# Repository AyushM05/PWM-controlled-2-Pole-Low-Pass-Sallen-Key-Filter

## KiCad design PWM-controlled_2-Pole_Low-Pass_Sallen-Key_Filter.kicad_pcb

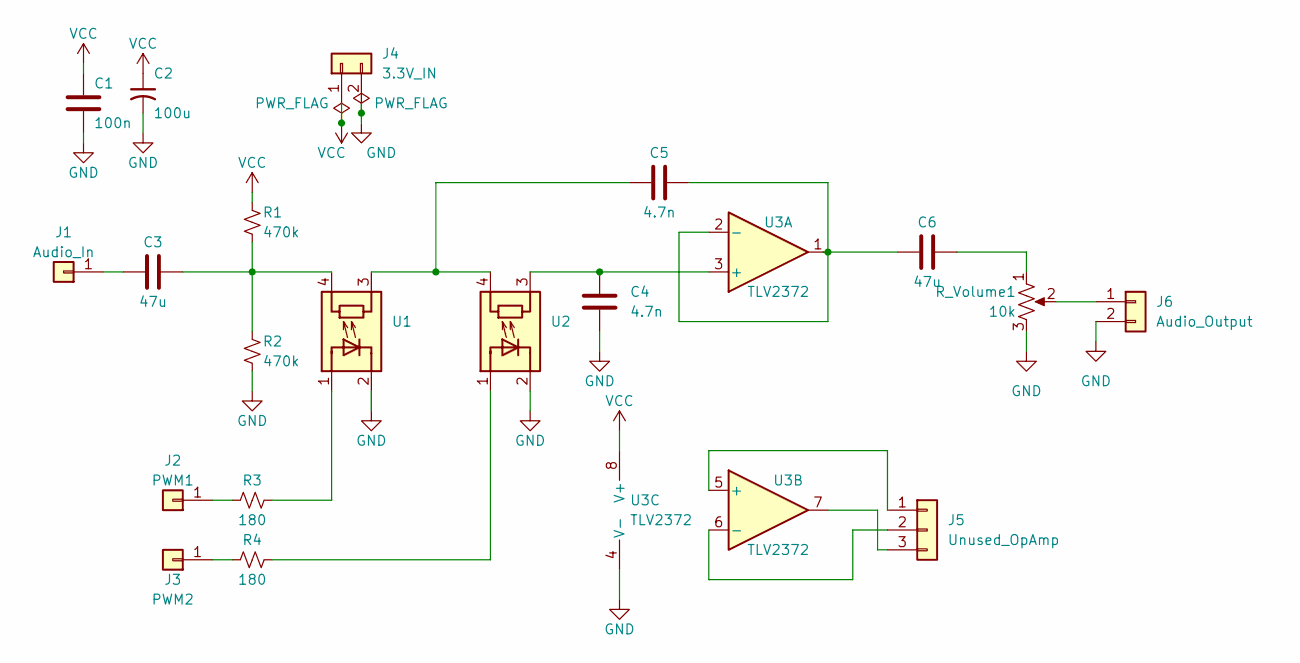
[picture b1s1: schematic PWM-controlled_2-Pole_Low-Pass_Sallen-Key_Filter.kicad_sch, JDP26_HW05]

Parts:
C1: 100n; 445-FG18X7R1H104KNT00-ND
C2: 100u; CP_Radial_D6.3mm_P2.50mm
C3, C6: 47u; CAP_RDEC71E476MWK1H03B
C4, C5: 4.7n; 445-181214-ND
J1: Audio_In; PinHeader_1x01_P2.54mm_Vertical
J2: PWM1; PinHeader_1x01_P2.54mm_Vertical
J3: PWM2; PinHeader_1x01_P2.54mm_Vertical
J4: 3.3V_IN; PinHeader_1x02_P2.54mm_Vertical
J5: Unused_OpAmp; PinHeader_1x03_P2.54mm_Vertical
J6: Audio_Output; PinHeader_1x02_P2.54mm_Vertical
R1, R2: 470k; R_Axial_DIN0309_L9.0mm_D3.2mm_P25.40mm_Horizontal
R3, R4: 180; R_Axial_DIN0309_L9.0mm_D3.2mm_P25.40mm_Horizontal
R_Volume1: 10k; Potentiometer_Bourns_PTV09A-1_Single_Vertical
U1, U2: NSL-32; Luna_NSL-32
U3: TLV2372; DIP-8_W7.62mm

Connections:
GND: C1.2, C2.2, C4.1, J4.2, J6.2, R2.2, R_Volume1.3, U1.2 (K), U2.2 (K), U3.4 (V-)
unnamed: C3.2, R1.2, R2.1, U1.4 (R)
unnamed: C5.2, U1.3 (R), U2.4 (R)
unnamed: C6.1, R_Volume1.1
unnamed: C3.1, J1.1
unnamed: J2.1, R3.1
unnamed: J3.1, R4.1
unnamed: J5.1, U3.5 (+)
unnamed: J5.2, U3.6 (-)
unnamed: J5.3, U3.7
unnamed: J6.1, R_Volume1.2
unnamed: R3.2, U1.1 (A)
unnamed: R4.2, U2.1 (A)
unnamed: C4.2, U2.3 (R), U3.3 (+)
unnamed: C5.1, C6.2, U3.1, U3.2 (-)
VCC: C1.1, C2.1, J4.1, R1.1, U3.8 (V+)

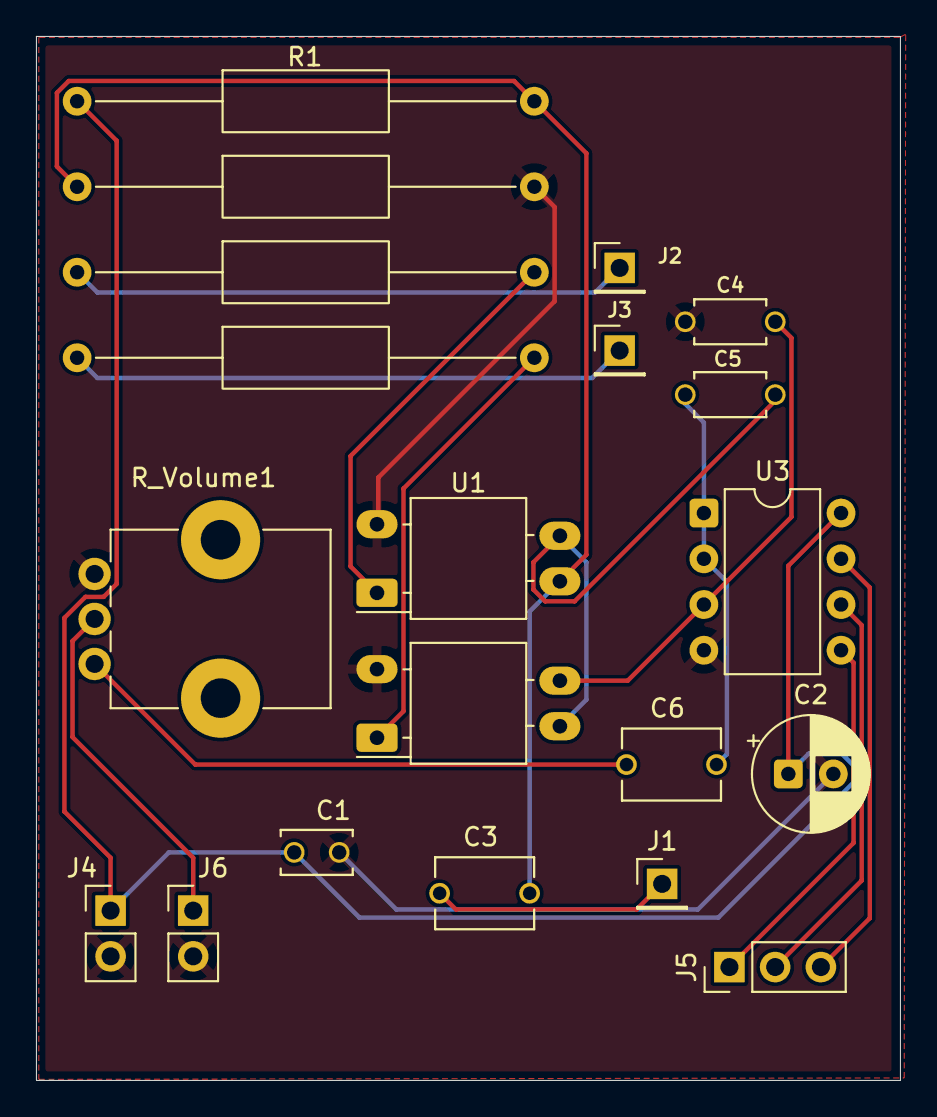
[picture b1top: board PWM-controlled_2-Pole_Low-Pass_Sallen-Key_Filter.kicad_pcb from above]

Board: 2 copper layers, 48.0 x 58.0 mm, 20 parts (0 on the bottom side), 16 nets.

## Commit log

2026-03-04 initial commit after reset
2026-03-04 HOPEFULLY WOPRKS
2026-03-04 (hopefully) finished schematic and footprints
2026-03-04 added digikey footprint for C2 and C3
2026-03-04 Open and closed file
2026-03-04 added footprints for R_Volume and U3B
2026-03-04 Added PWR_FLAG and got rid of ERC error
2026-03-04 CLEAN ERC NO ERRORS
2026-03-05 COMPLETE LAYOUT & CLEAN DRC
